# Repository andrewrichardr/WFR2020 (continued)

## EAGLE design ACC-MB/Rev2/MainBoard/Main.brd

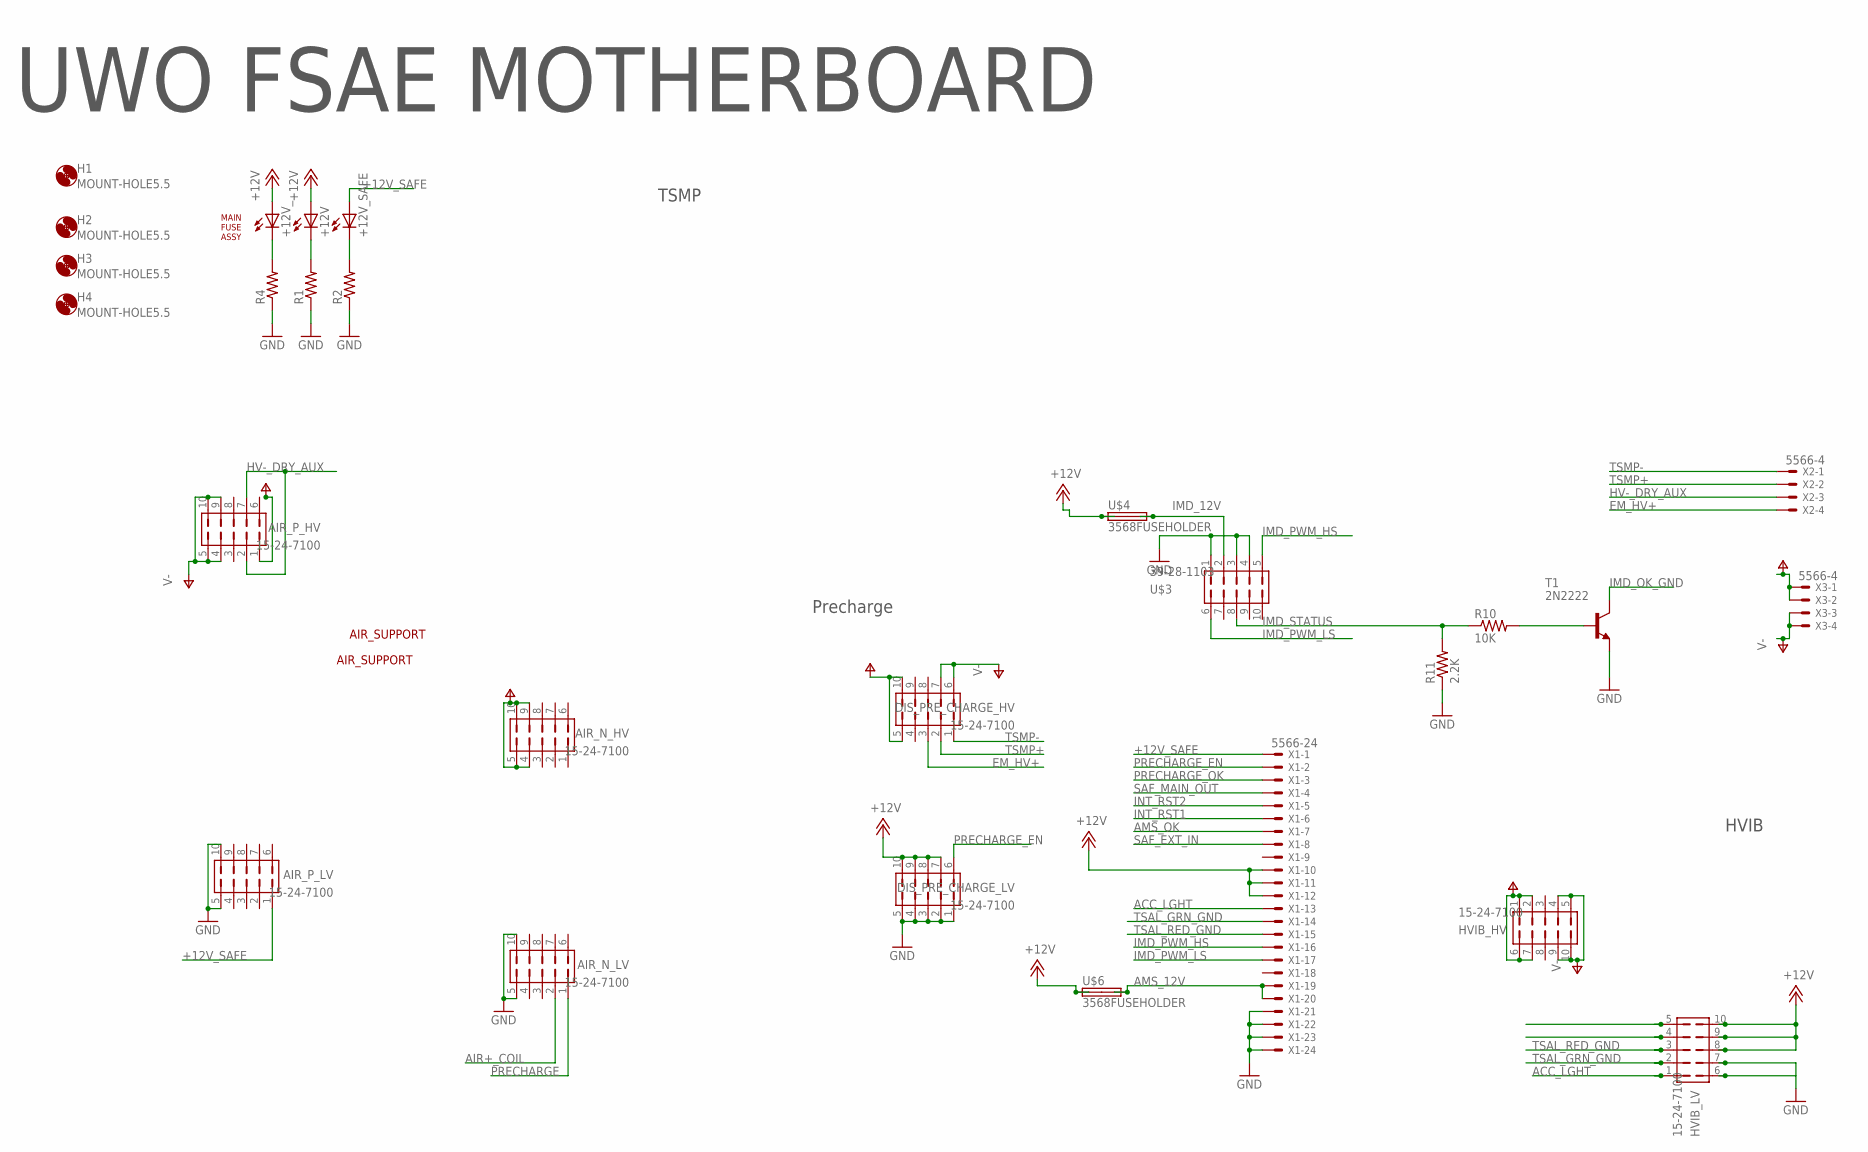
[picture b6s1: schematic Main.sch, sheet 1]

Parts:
+12V, +12V_, +12V_SAFE: LED3MM
AIR_N_HV: 15-24-7100; 5566-10-BMI
AIR_N_LV: 15-24-7100; 5566-10-BMI
AIR_P_HV: 15-24-7100; 5566-10-BMI
AIR_P_LV: 15-24-7100; 5566-10-BMI
DIS_PRE_CHARGE_HV: 15-24-7100; 5566-10-BMI
DIS_PRE_CHARGE_LV: 15-24-7100; 5566-10-BMI
H1, H2, H3, H4: MOUNT-HOLE5.5; 5,5
HVIB_HV: 15-24-7100; 5566-10-BMI
HVIB_LV: 15-24-7100; 5566-10-BMI
R1, R2, R4: R-US_R0805; R0805
R10: 10K; M0805
R11: 2.2K; M0805
T1: 2N2222; TO92-EBC-OVAL
U$1: MAINFUSEASSY
U$3: 39-28-1103
U$4, U$6: 3568FUSEHOLDER; 3568
U$7, U$8: AIR_SUPPORT
X1: 5566-24
X2, X3: 5566-4

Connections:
+12V: +12V.A, +12V_.A, DIS_PRE_CHARGE_LV.7, DIS_PRE_CHARGE_LV.8, DIS_PRE_CHARGE_LV.9, DIS_PRE_CHARGE_LV.10, HVIB_LV.8, HVIB_LV.9, HVIB_LV.10, U$4.L1 (1A), U$4.L2 (1B), U$6.L1 (1A), U$6.L2 (1B), X1.10, X1.11, X1.12; also elsewhere on the board
+12V_SAFE: +12V_SAFE.A, AIR_P_LV.1, X1.1; also elsewhere on the board
ACC_LGHT: HVIB_LV.1, X1.13
AIR+_COIL: AIR_N_LV.2; also elsewhere on the board
AMS_12V: U$6.R1 (2A), U$6.R2 (2B), X1.19, X1.20
AMS_OK: X1.7; also elsewhere on the board
EM_HV+: DIS_PRE_CHARGE_HV.3, X2.4
GND: AIR_N_LV.5, AIR_N_LV.10, AIR_P_LV.5, AIR_P_LV.10, DIS_PRE_CHARGE_LV.1, DIS_PRE_CHARGE_LV.2, DIS_PRE_CHARGE_LV.3, DIS_PRE_CHARGE_LV.4, DIS_PRE_CHARGE_LV.5, HVIB_LV.7, R1.1, R2.1, R4.1, R11.1, T1.E, U$3.1, U$3.3, U$3.4, X1.21, X1.22, X1.23, X1.24; also elsewhere on the board
HV-_DRY_AUX: AIR_P_HV.2, AIR_P_HV.7, X2.3
IMD_12V: U$3.2, U$4.R1 (2A), U$4.R2 (2B)
IMD_OK_GND: T1.C; also elsewhere on the board
IMD_PWM_HS: U$3.5, X1.16
IMD_PWM_LS: U$3.6, X1.17
IMD_STATUS: R10.1, R11.2, U$3.8
INT_RST1: X1.6; also elsewhere on the board
INT_RST2: X1.5; also elsewhere on the board
unnamed: +12V.K (C), R1.2
unnamed: R10.2, T1.B
unnamed: +12V_.K (C), R4.2
unnamed: +12V_SAFE.K (C), R2.2
PRECHARGE: AIR_N_LV.1; also elsewhere on the board
PRECHARGE_EN: DIS_PRE_CHARGE_LV.6, X1.2; also elsewhere on the board
PRECHARGE_OK: X1.3; also elsewhere on the board
SAF_EXT_IN: X1.8; also elsewhere on the board
SAF_MAIN_OUT: X1.4; also elsewhere on the board
TSAL_GRN_GND: HVIB_LV.2, X1.14
TSAL_RED_GND: HVIB_LV.3, X1.15
TSMP+: DIS_PRE_CHARGE_HV.2, X2.2
TSMP-: DIS_PRE_CHARGE_HV.1, X2.1
V+: AIR_N_HV.4, AIR_N_HV.5, AIR_N_HV.9, AIR_N_HV.10, AIR_P_HV.1, AIR_P_HV.6, DIS_PRE_CHARGE_HV.5, DIS_PRE_CHARGE_HV.10, HVIB_HV.1, HVIB_HV.2, HVIB_HV.6, HVIB_HV.7, X3.1, X3.2
V-: AIR_P_HV.4, AIR_P_HV.5, AIR_P_HV.9, AIR_P_HV.10, DIS_PRE_CHARGE_HV.6, DIS_PRE_CHARGE_HV.7, HVIB_HV.4, HVIB_HV.5, HVIB_HV.9, HVIB_HV.10, X3.3, X3.4

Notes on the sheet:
UWO FSAE MOTHERBOARD
TSMP
Precharge
HVIB

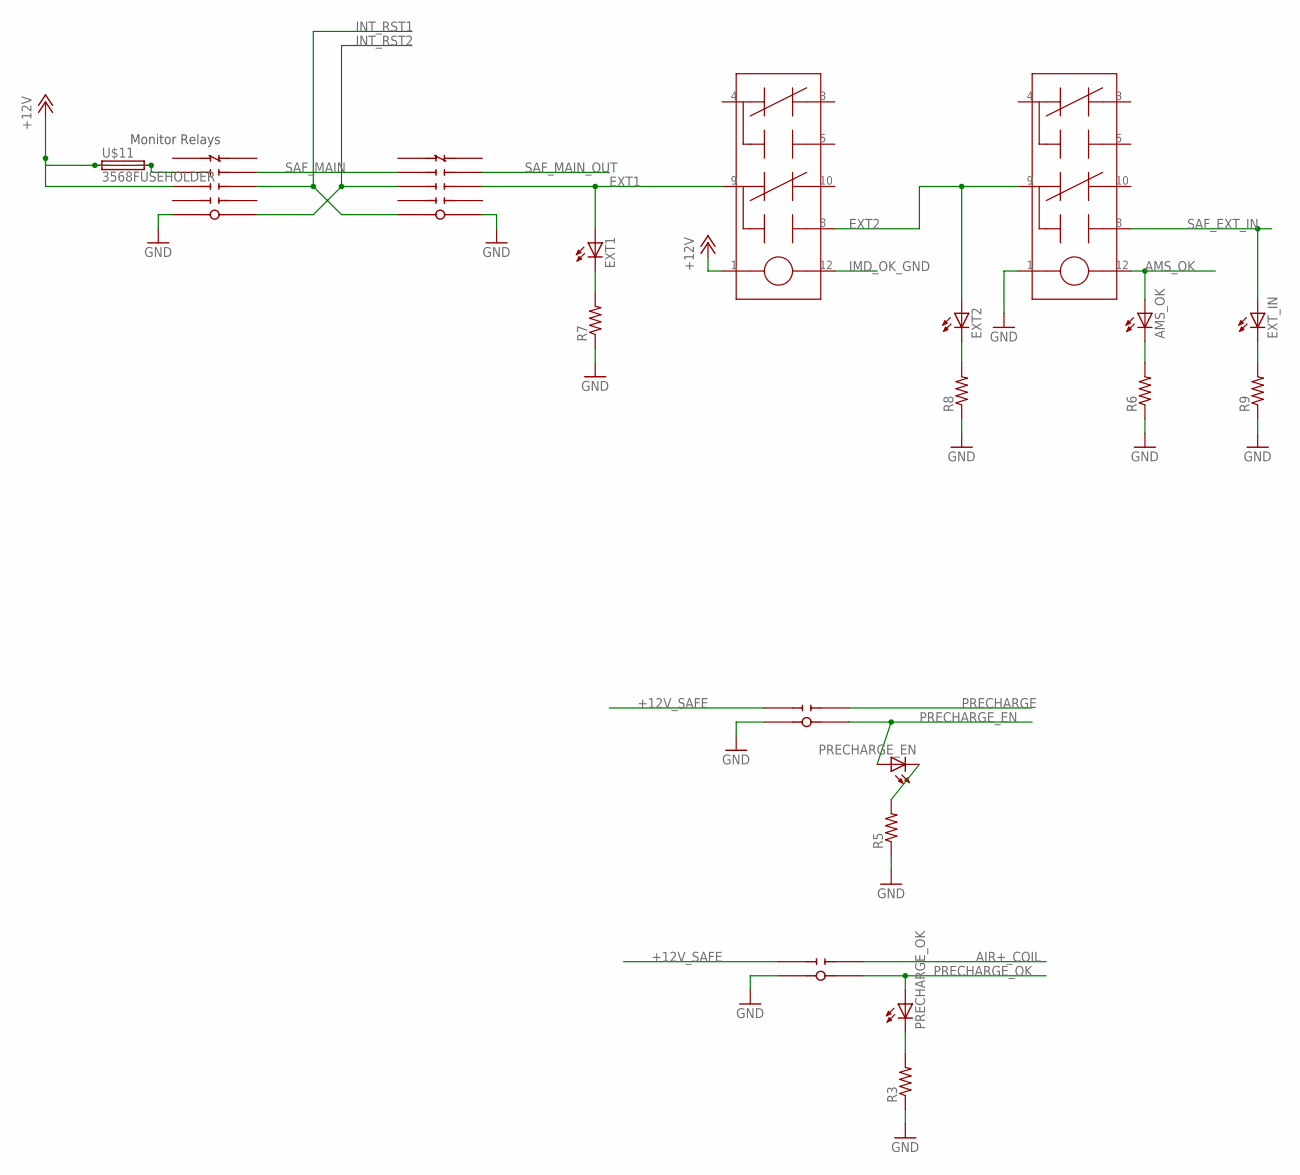
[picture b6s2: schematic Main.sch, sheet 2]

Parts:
AMS_OK: LED3MM
EXT1, EXT2: LED3MM
EXT_IN: LED3MM
PRECHARGE_EN: LED3MM
PRECHARGE_OK: LED3MM
R3, R5, R6, R7, R8, R9: R-US_R0805; R0805
U$2, U$5: SR4M4012_TE; SR4M4012_FOOT
U$9, U$10: G5NB-1A-E
U$11: 3568FUSEHOLDER; 3568
U$12, U$13: V23079B1203B301

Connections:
+12V: U$2.NOA2, U$11.L1 (1A), U$11.L2 (1B), U$12.1; also elsewhere on the board
+12V_SAFE: U$9.2 (NOA1), U$10.2 (NOA1); also elsewhere on the board
AIR+_COIL: U$9.3 (NOB1); also elsewhere on the board
AMS_OK: AMS_OK.A, U$13.12; also elsewhere on the board
EXT1: EXT1.A, U$5.NOB2, U$12.9
EXT2: EXT2.A, U$12.8, U$13.9
GND: R3.1, R5.1, R6.1, R7.1, R8.1, R9.1, U$2.COIL+, U$5.COIL-, U$9.1 (COIL+), U$10.1 (COIL+), U$13.1; also elsewhere on the board
IMD_OK_GND: U$12.12; also elsewhere on the board
INT_RST1: U$2.NOB2, U$5.COIL+; also elsewhere on the board
INT_RST2: U$2.COIL-, U$5.NOA2; also elsewhere on the board
unnamed: U$2.NOA3, U$11.R1 (2A), U$11.R2 (2B)
unnamed: PRECHARGE_EN.K (C), R5.2
unnamed: PRECHARGE_OK.K (C), R3.2
unnamed: AMS_OK.K (C), R6.2
unnamed: EXT1.K (C), R7.2
unnamed: EXT2.K (C), R8.2
unnamed: EXT_IN.K (C), R9.2
PRECHARGE: U$10.3 (NOB1); also elsewhere on the board
PRECHARGE_EN: PRECHARGE_EN.A, U$10.4 (COIL-); also elsewhere on the board
PRECHARGE_OK: PRECHARGE_OK.A, U$9.4 (COIL-); also elsewhere on the board
SAF_EXT_IN: EXT_IN.A, U$13.8; also elsewhere on the board
SAF_MAIN: U$2.NOB3, U$5.NOA3
SAF_MAIN_OUT: U$5.NOB3; also elsewhere on the board

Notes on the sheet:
Monitor Relays

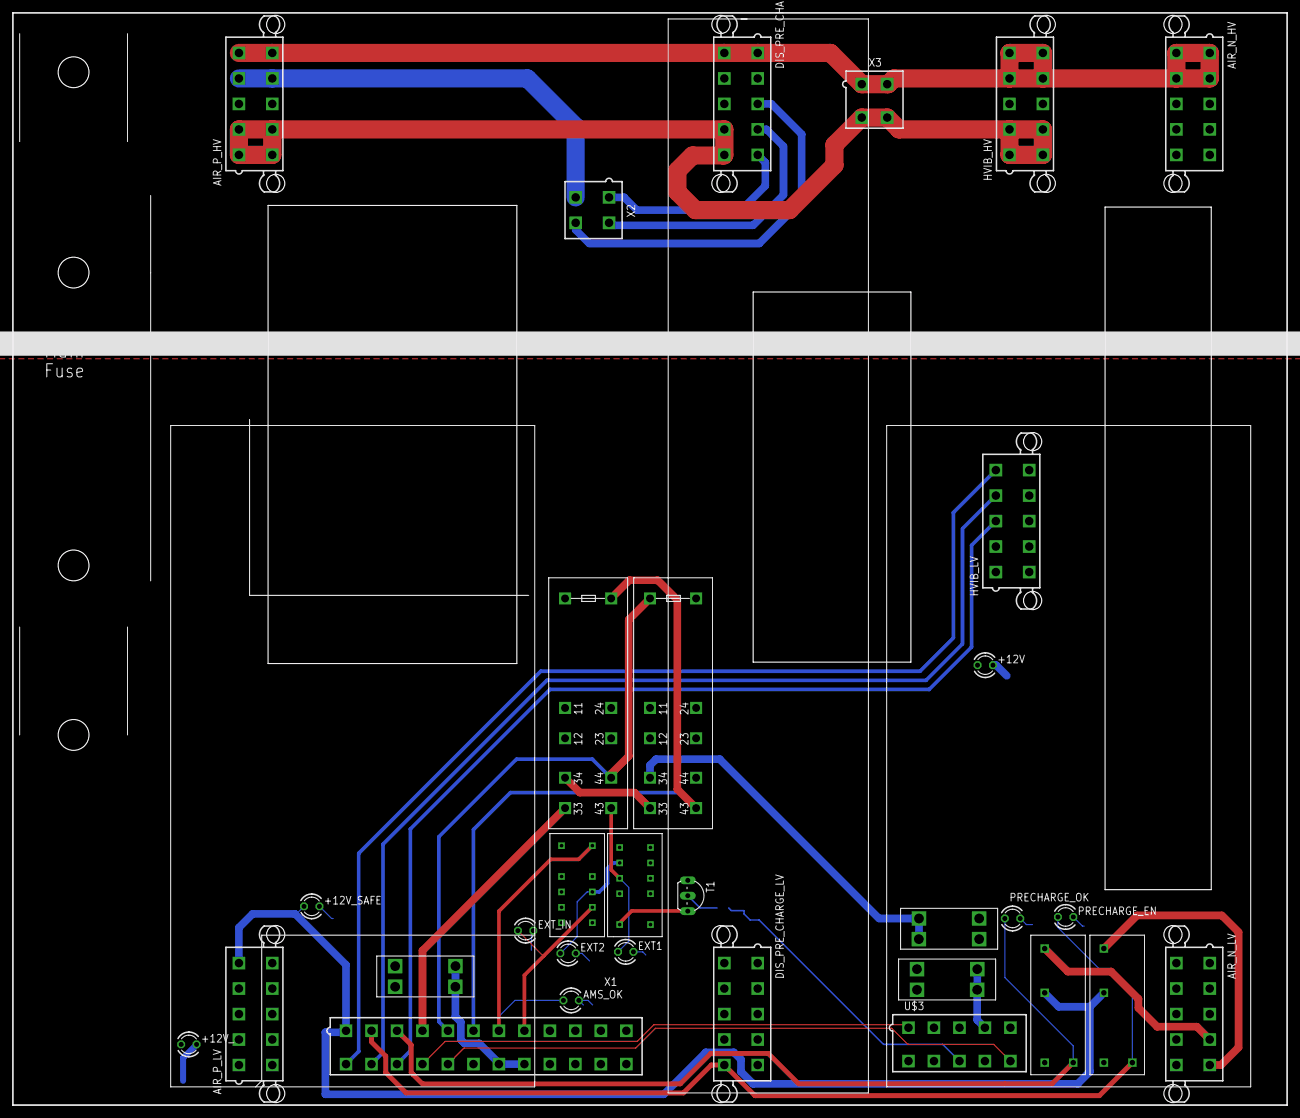
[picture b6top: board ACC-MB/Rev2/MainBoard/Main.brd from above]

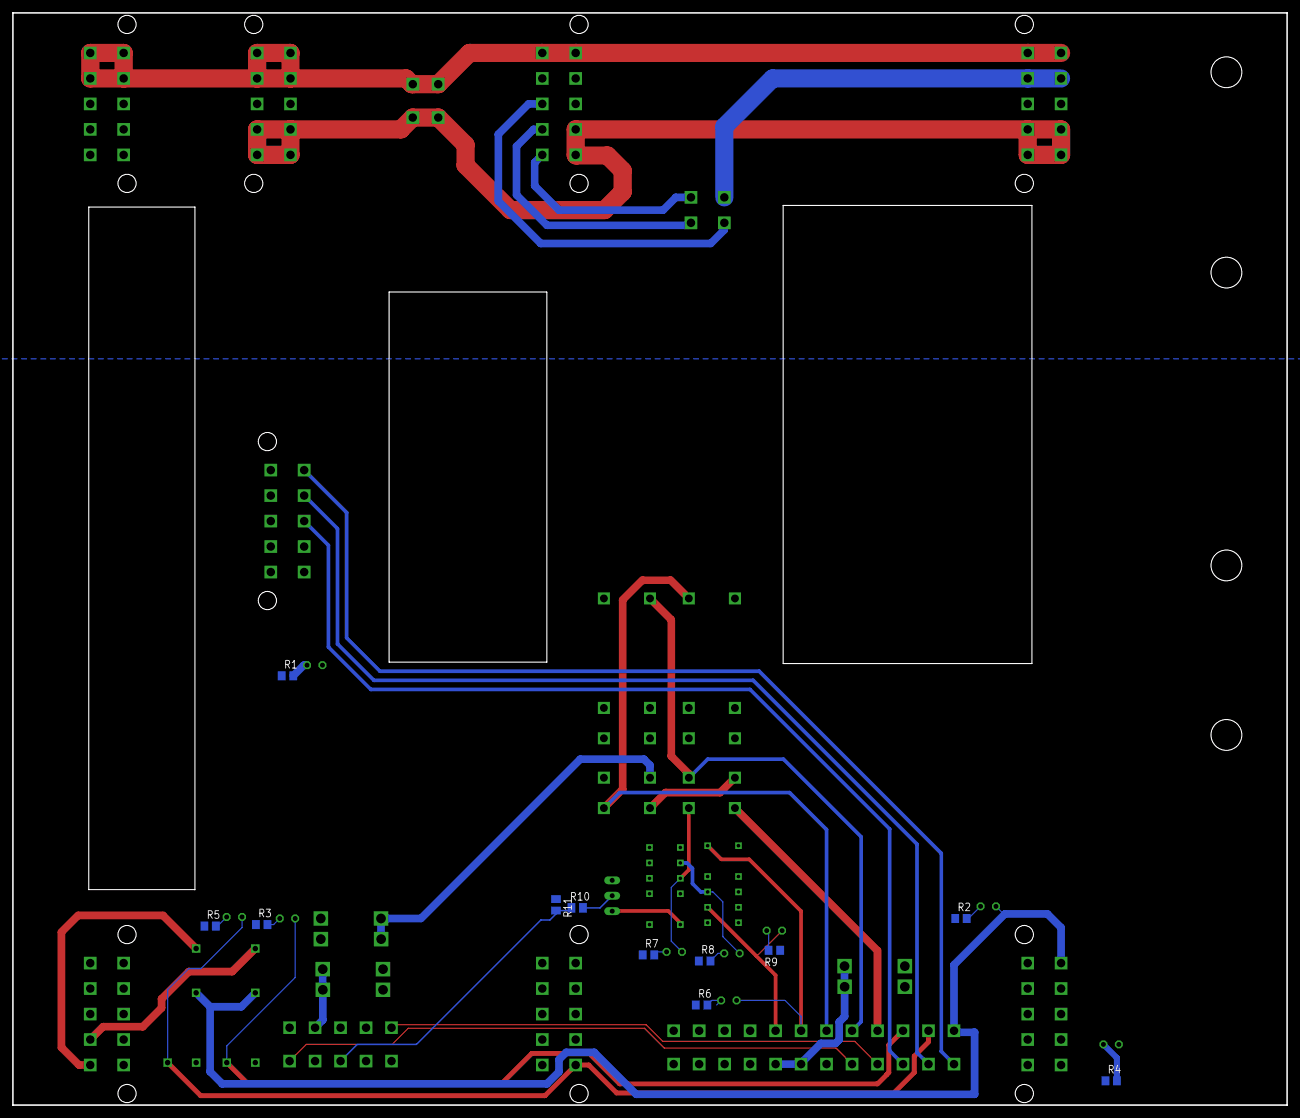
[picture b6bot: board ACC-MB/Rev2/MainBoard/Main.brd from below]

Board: 2 copper layers, 210.0 x 180.0 mm, 49 parts (11 on the bottom side), 41 nets.

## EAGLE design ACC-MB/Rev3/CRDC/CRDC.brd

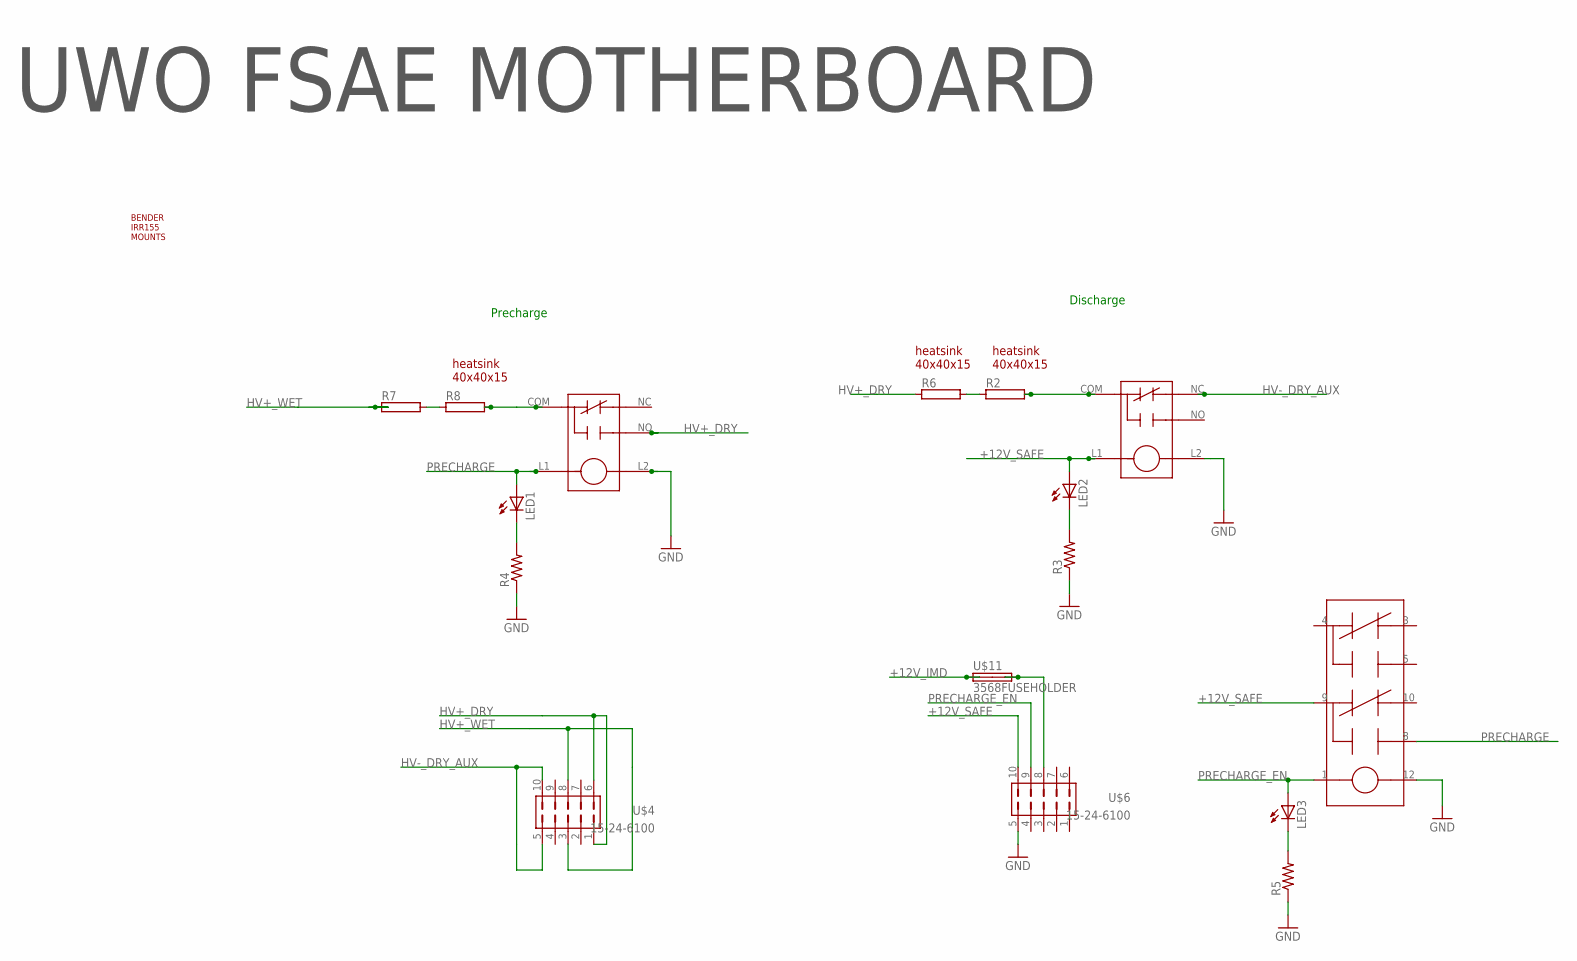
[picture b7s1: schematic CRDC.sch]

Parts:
LED1, LED2, LED3: LED3MM
R2, R6, R7, R8: RMG100-H; TO-247-2H
R3, R4, R5: R-US_R0805; R0805
U$1, U$2: G81C335
U$4, U$6: 15-24-6100
U$5, U$8, U$9: HEATSINK40X40X15
U$7: V23079B1203B301
U$10: BENDER_IRR155
U$11: 3568FUSEHOLDER; 3568

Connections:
+12V_IMD: U$11.L1 (1A), U$11.L2 (1B)
+12V_SAFE: LED2.A, U$2.L1, U$6.10, U$7.9
GND: R3.1, R4.1, R5.1, U$1.L2, U$2.L2, U$6.5, U$7.12
HV+_DRY: R6.1, U$1.NO, U$4.1, U$4.6
HV+_WET: R7.1, U$4.3, U$4.8
HV-_DRY_AUX: U$2.NC, U$4.5, U$4.10
unnamed: LED2.K (C), R3.2
unnamed: LED3.K (C), R5.2
unnamed: U$6.8, U$11.R1 (2A), U$11.R2 (2B)
unnamed: R2.2, U$2.COM
unnamed: LED1.K (C), R4.2
unnamed: R2.1, R6.2
unnamed: R7.2, R8.1
unnamed: R8.2, U$1.COM
PRECHARGE: LED1.A, U$1.L1, U$7.8
PRECHARGE_EN: LED3.A, U$6.9, U$7.1

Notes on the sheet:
UWO FSAE MOTHERBOARD
Precharge
Discharge

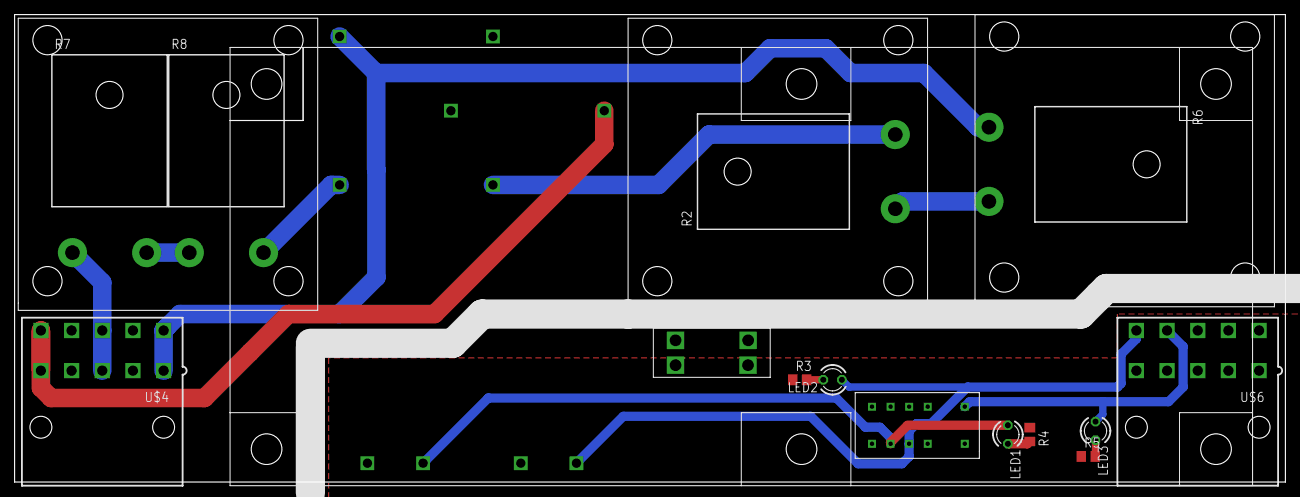
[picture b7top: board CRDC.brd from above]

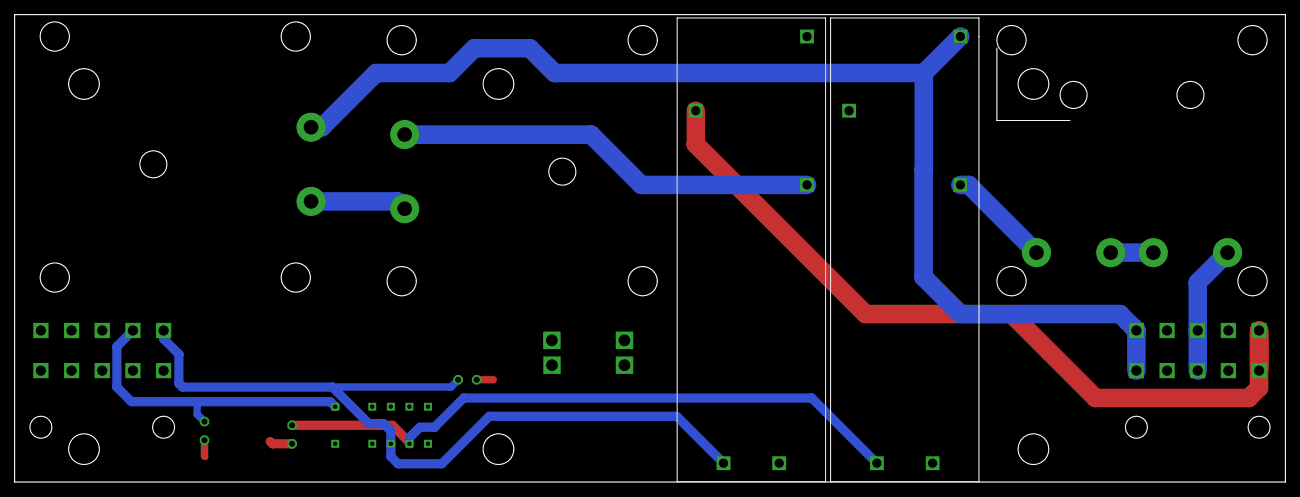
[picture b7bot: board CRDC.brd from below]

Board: 2 copper layers, 174.0 x 64.0 mm, 20 parts (2 on the bottom side), 16 nets.
